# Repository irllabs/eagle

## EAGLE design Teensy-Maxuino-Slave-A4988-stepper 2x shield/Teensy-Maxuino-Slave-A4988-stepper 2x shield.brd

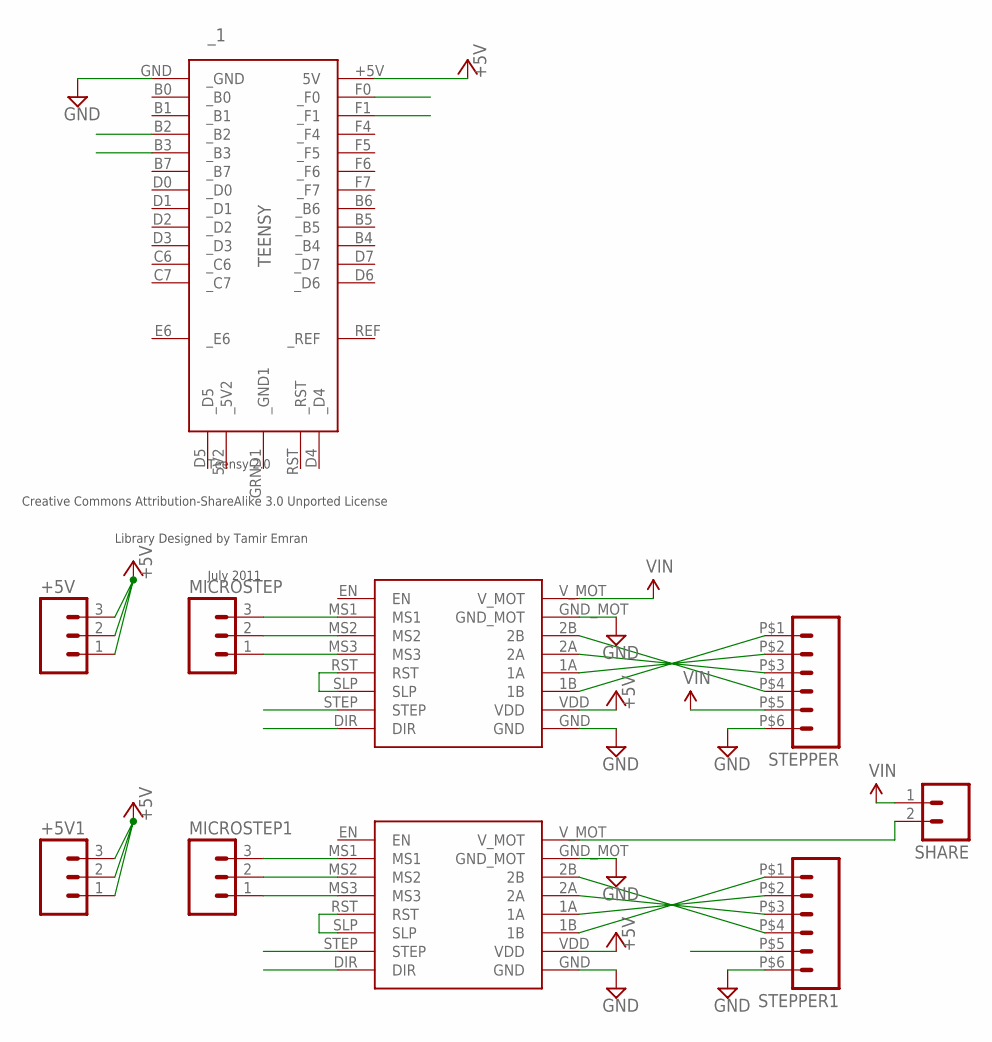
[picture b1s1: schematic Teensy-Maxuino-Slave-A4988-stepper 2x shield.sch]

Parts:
+5V, +5V1: M03PTH; 1X03
A4988_1, A4988_2: POLOLU_A4988
MICROSTEP, MICROSTEP1: M03PTH; 1X03
SHARE: M02PTH; 1X02
STEPPER, STEPPER1: M06; SPRINGTERMINAL-2.54MM-6
_1: TEENSY

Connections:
+5V: +5V.1, +5V.2, +5V.3, +5V1.1, +5V1.2, +5V1.3, A4988_1.VDD, A4988_2.VDD, _1.+5V (5V)
DIR: A4988_1.DIR, _1.F0 (_F0)
DIR1: A4988_2.DIR, _1.B3 (_B3)
GND: A4988_1.GND, A4988_1.GND_MOT, A4988_2.GND, A4988_2.GND_MOT, STEPPER.P$6 (6), STEPPER1.P$6 (6), _1.GND (_GND)
unnamed: A4988_1.2B, STEPPER.P$4 (4)
unnamed: A4988_1.2A, STEPPER.P$3 (3)
unnamed: A4988_1.1A, STEPPER.P$2 (2)
unnamed: A4988_1.1B, STEPPER.P$1 (1)
unnamed: A4988_2.RST, A4988_2.SLP
unnamed: A4988_1.RST, A4988_1.SLP
unnamed: A4988_2.MS1, MICROSTEP1.3
unnamed: A4988_1.MS1, MICROSTEP.3
unnamed: A4988_1.MS2, MICROSTEP.2
unnamed: A4988_1.MS3, MICROSTEP.1
unnamed: A4988_2.MS2, MICROSTEP1.2
unnamed: A4988_2.MS3, MICROSTEP1.1
unnamed: A4988_2.2B, STEPPER1.P$4 (4)
unnamed: A4988_2.2A, STEPPER1.P$3 (3)
unnamed: A4988_2.1A, STEPPER1.P$2 (2)
unnamed: A4988_2.1B, STEPPER1.P$1 (1)
STEP: A4988_1.STEP, _1.F1 (_F1)
STEP1: A4988_2.STEP, _1.B2 (_B2)
VIN: A4988_1.V_MOT, SHARE.1, STEPPER.P$5 (5)
VIN_2: A4988_2.V_MOT, SHARE.2, STEPPER1.P$5 (5)

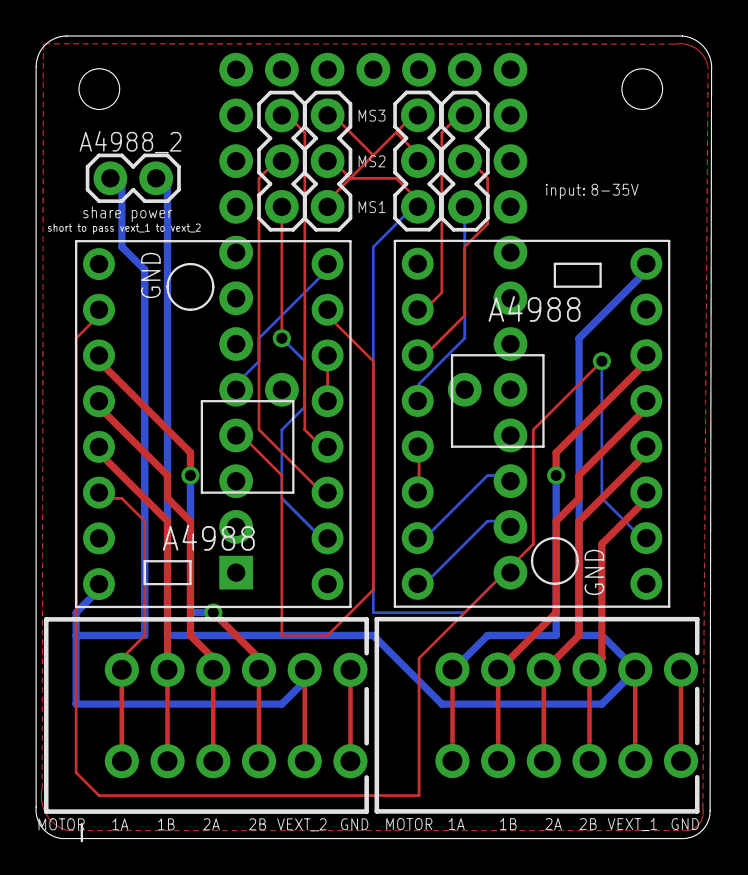
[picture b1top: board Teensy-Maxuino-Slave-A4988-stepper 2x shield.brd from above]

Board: 2 copper layers, 37.5 x 44.6 mm, 10 parts (1 on the bottom side), 24 nets.

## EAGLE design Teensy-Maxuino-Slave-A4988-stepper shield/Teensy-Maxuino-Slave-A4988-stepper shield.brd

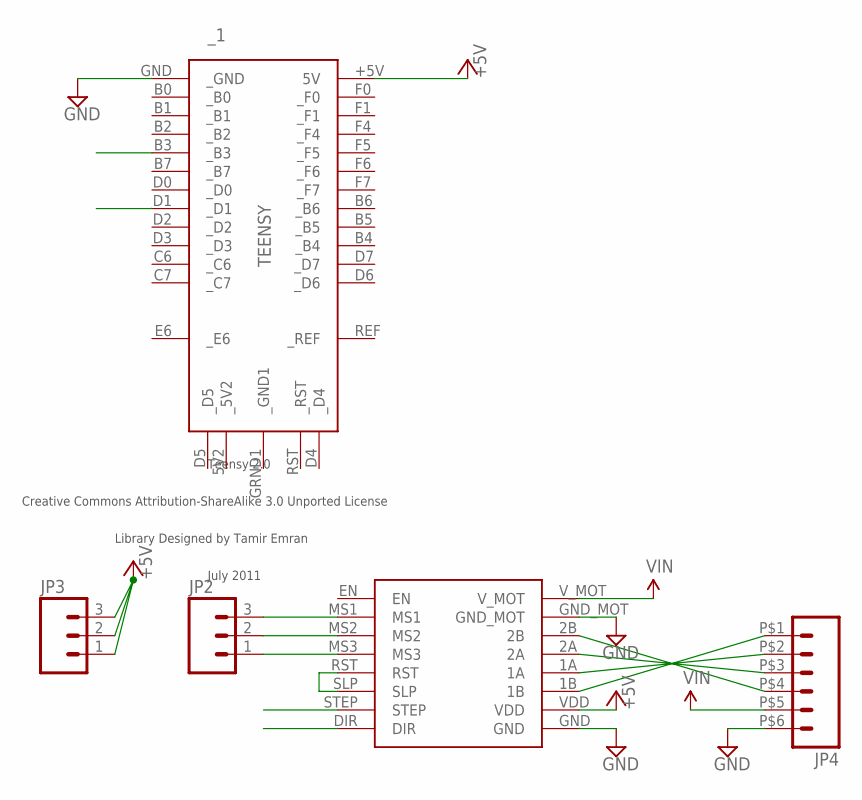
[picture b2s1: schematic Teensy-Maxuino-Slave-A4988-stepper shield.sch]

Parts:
JP2, JP3: M03PTH; 1X03
JP4: M06; SPRINGTERMINAL-2.54MM-6
U$1: POLOLU_A4988
_1: TEENSY

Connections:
+5V: JP3.1, JP3.2, JP3.3, U$1.VDD, _1.+5V (5V)
DIR: U$1.DIR, _1.D1 (_D1)
GND: JP4.P$6 (6), U$1.GND, U$1.GND_MOT, _1.GND (_GND)
unnamed: JP4.P$4 (4), U$1.2B
unnamed: JP4.P$3 (3), U$1.2A
unnamed: JP4.P$2 (2), U$1.1A
unnamed: JP4.P$1 (1), U$1.1B
unnamed: U$1.RST, U$1.SLP
unnamed: JP2.3, U$1.MS1
unnamed: JP2.2, U$1.MS2
unnamed: JP2.1, U$1.MS3
STEP: U$1.STEP, _1.B3 (_B3)
VIN: JP4.P$5 (5), U$1.V_MOT

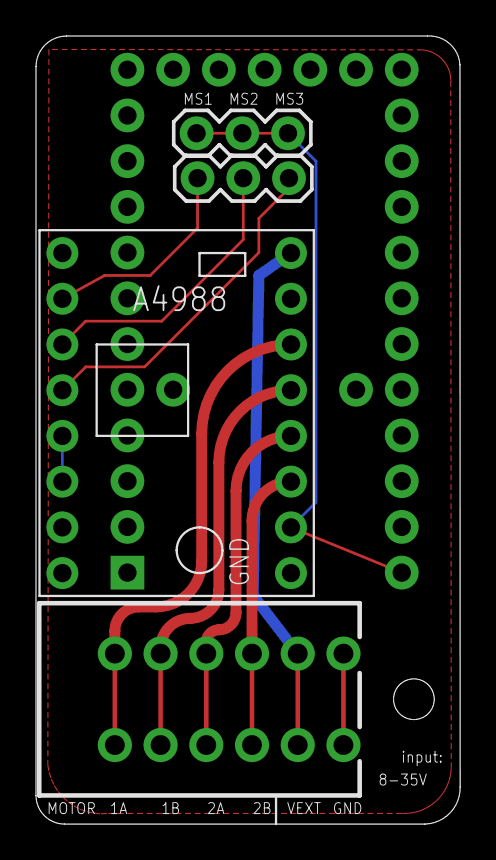
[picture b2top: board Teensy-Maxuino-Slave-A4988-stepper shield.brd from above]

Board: 2 copper layers, 23.6 x 43.8 mm, 5 parts (1 on the bottom side), 13 nets.

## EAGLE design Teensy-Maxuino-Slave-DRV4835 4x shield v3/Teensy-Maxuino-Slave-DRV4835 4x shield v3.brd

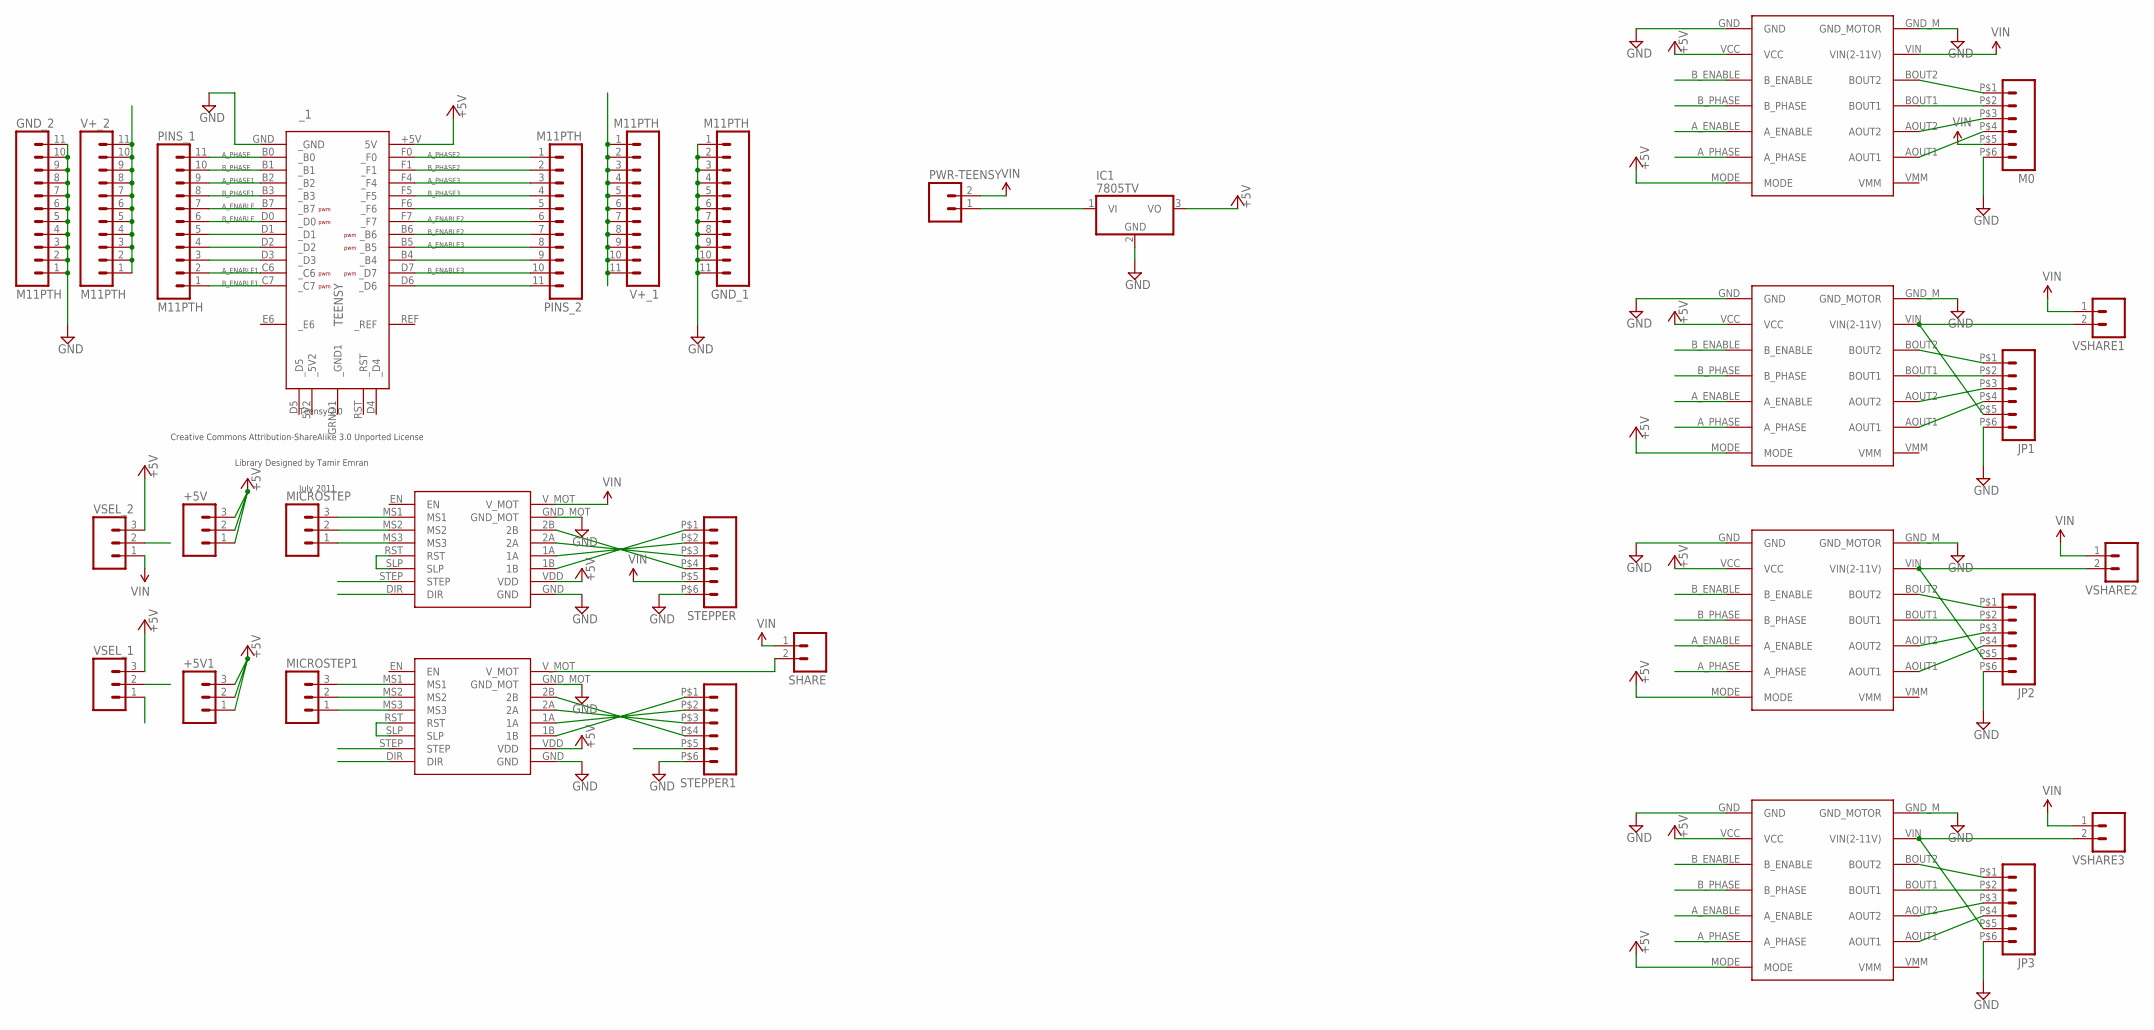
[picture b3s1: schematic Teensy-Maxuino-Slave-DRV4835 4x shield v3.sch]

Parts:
+5V, +5V1: M03PTH; 1X03
A4988_1, A4988_2: POLOLU_A4988
DRV0, DRV1, DRV2, DRV3: POLOLU_DRV8835
GND_1, GND_2: M11PTH; 1X11
IC1: 7805TV; TO220V
JP1, JP2, JP3: M06; SPRINGTERMINAL-2.54MM-6
M0: M06; SPRINGTERMINAL-2.54MM-6
MICROSTEP, MICROSTEP1: M03PTH; 1X03
PINS_1, PINS_2: M11PTH; 1X11
PWR-TEENSY: M02PTH; 1X02
SHARE: M02PTH; 1X02
STEPPER, STEPPER1: M06; SPRINGTERMINAL-2.54MM-6
V+_1, V+_2: M11PTH; 1X11
VSEL_1, VSEL_2: M03PTH; 1X03
VSHARE1, VSHARE2, VSHARE3: M02PTH; 1X02
_1: TEENSY

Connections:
+5V: +5V.1, +5V.2, +5V.3, +5V1.1, +5V1.2, +5V1.3, A4988_1.VDD, A4988_2.VDD, DRV0.MODE, DRV0.VCC, DRV1.MODE, DRV1.VCC, DRV2.MODE, DRV2.VCC, DRV3.MODE, DRV3.VCC, IC1.3 (VO), VSEL_1.3, VSEL_2.3, _1.+5V (5V)
ATTRU: JP1.P$6 (6), JP2.P$6 (6), JP3.P$6 (6), M0.P$6 (6)
A_ENABLE: DRV0.A_ENABLE, PINS_1.7, _1.B7 (_B7)
A_ENABLE1: DRV1.A_ENABLE, PINS_1.2, _1.C6 (_C6)
A_ENABLE2: DRV2.A_ENABLE, PINS_2.6, _1.F7 (_F7)
A_ENABLE3: DRV3.A_ENABLE, PINS_2.8, _1.B5 (_B5)
A_PHASE: DRV0.A_PHASE, PINS_1.11, _1.B0 (_B0)
A_PHASE1: DRV1.A_PHASE, PINS_1.9, _1.B2 (_B2)
A_PHASE2: DRV2.A_PHASE, PINS_2.1, _1.F0 (_F0)
A_PHASE3: DRV3.A_PHASE, PINS_2.3, _1.F4 (_F4)
B_ENABLE: DRV0.B_ENABLE, PINS_1.6, _1.D0 (_D0)
B_ENABLE1: DRV1.B_ENABLE, PINS_1.1, _1.C7 (_C7)
B_ENABLE2: DRV2.B_ENABLE, PINS_2.7, _1.B6 (_B6)
B_ENABLE3: DRV3.B_ENABLE, PINS_2.10, _1.D7 (_D7)
B_PHASE: DRV0.B_PHASE, PINS_1.10, _1.B1 (_B1)
B_PHASE1: DRV1.B_PHASE, PINS_1.4, PINS_1.8, _1.B3 (_B3), _1.D2 (_D2)
B_PHASE2: DRV2.B_PHASE, PINS_2.2, _1.F1 (_F1)
B_PHASE3: DRV3.B_PHASE, PINS_2.4, _1.F5 (_F5)
DIR: A4988_1.DIR, PINS_2.11, _1.D6 (_D6)
DIR1: A4988_2.DIR, PINS_1.5, _1.D1 (_D1)
GND: A4988_1.GND, A4988_1.GND_MOT, A4988_2.GND, A4988_2.GND_MOT, DRV0.GND, DRV0.GND_M (GND_MOTOR), DRV1.GND, DRV1.GND_M (GND_MOTOR), DRV2.GND, DRV2.GND_M (GND_MOTOR), DRV3.GND, DRV3.GND_M (GND_MOTOR), GND_1.1, GND_1.2, GND_1.3, GND_1.4, GND_1.5, GND_1.6, GND_1.7, GND_1.8, GND_1.9, GND_1.10, GND_1.11, GND_2.1, GND_2.2, GND_2.3, GND_2.4, GND_2.5, GND_2.6, GND_2.7, GND_2.8, GND_2.9, GND_2.10, GND_2.11, IC1.2 (GND), STEPPER.P$6 (6), STEPPER1.P$6 (6), _1.GND (_GND)
unnamed: A4988_1.2B, STEPPER.P$4 (4)
unnamed: A4988_1.2A, STEPPER.P$3 (3)
unnamed: A4988_1.1A, STEPPER.P$2 (2)
unnamed: A4988_1.1B, STEPPER.P$1 (1)
unnamed: A4988_2.RST, A4988_2.SLP
unnamed: A4988_1.RST, A4988_1.SLP
unnamed: A4988_2.MS1, MICROSTEP1.3
unnamed: A4988_1.MS1, MICROSTEP.3
unnamed: A4988_1.MS2, MICROSTEP.2
unnamed: A4988_1.MS3, MICROSTEP.1
unnamed: A4988_2.MS2, MICROSTEP1.2
unnamed: A4988_2.MS3, MICROSTEP1.1
unnamed: A4988_2.2B, STEPPER1.P$4 (4)
unnamed: A4988_2.2A, STEPPER1.P$3 (3)
unnamed: A4988_2.1A, STEPPER1.P$2 (2)
unnamed: A4988_2.1B, STEPPER1.P$1 (1)
unnamed: PINS_1.3, _1.D3 (_D3)
unnamed: PINS_2.5, _1.F6 (_F6)
unnamed: DRV0.AOUT1, M0.P$4 (4)
unnamed: DRV0.AOUT2, M0.P$3 (3)
unnamed: DRV0.BOUT1, M0.P$2 (2)
unnamed: DRV0.BOUT2, M0.P$1 (1)
unnamed: DRV1.AOUT1, JP1.P$4 (4)
unnamed: DRV1.AOUT2, JP1.P$3 (3)
unnamed: DRV1.BOUT1, JP1.P$2 (2)
unnamed: DRV1.BOUT2, JP1.P$1 (1)
unnamed: DRV2.AOUT1, JP2.P$4 (4)
unnamed: DRV2.AOUT2, JP2.P$3 (3)
unnamed: DRV2.BOUT1, JP2.P$2 (2)
unnamed: DRV2.BOUT2, JP2.P$1 (1)
unnamed: DRV3.AOUT1, JP3.P$4 (4)
unnamed: DRV3.AOUT2, JP3.P$3 (3)
unnamed: DRV3.BOUT1, JP3.P$2 (2)
unnamed: DRV3.BOUT2, JP3.P$1 (1)
unnamed: IC1.1 (VI), PWR-TEENSY.1
STEP: A4988_1.STEP, PINS_2.9, _1.B4 (_B4)
STEP1: A4988_2.STEP
V+_1: V+_1.1, V+_1.2, V+_1.3, V+_1.4, V+_1.5, V+_1.6, V+_1.7, V+_1.8, V+_1.9, V+_1.10, V+_1.11, VSEL_1.2
V+_2: V+_2.1, V+_2.2, V+_2.3, V+_2.4, V+_2.5, V+_2.6, V+_2.7, V+_2.8, V+_2.9, V+_2.10, V+_2.11, VSEL_2.2
VIN: A4988_1.V_MOT, DRV0.VIN (VIN(2-11V)), M0.P$5 (5), PWR-TEENSY.2, SHARE.1, STEPPER.P$5 (5), VSEL_2.1, VSHARE1.1, VSHARE2.1, VSHARE3.1
VIN1: DRV1.VIN (VIN(2-11V)), JP1.P$5 (5), VSHARE1.2
VIN2: DRV2.VIN (VIN(2-11V)), JP2.P$5 (5), VSHARE2.2
VIN3: DRV3.VIN (VIN(2-11V)), JP3.P$5 (5), VSHARE3.2
VIN_2: A4988_2.V_MOT, SHARE.2, STEPPER1.P$5 (5), VSEL_1.1

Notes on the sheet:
B_PHASE1
A_PHASE
B_PHASE
A_PHASE1
A_ENABLE
B_ENABLE
A_ENABLE1
B_ENABLE1
B_PHASE3
A_PHASE2
B_PHASE2
A_PHASE3
A_ENABLE2
B_ENABLE2
A_ENABLE3
B_ENABLE3

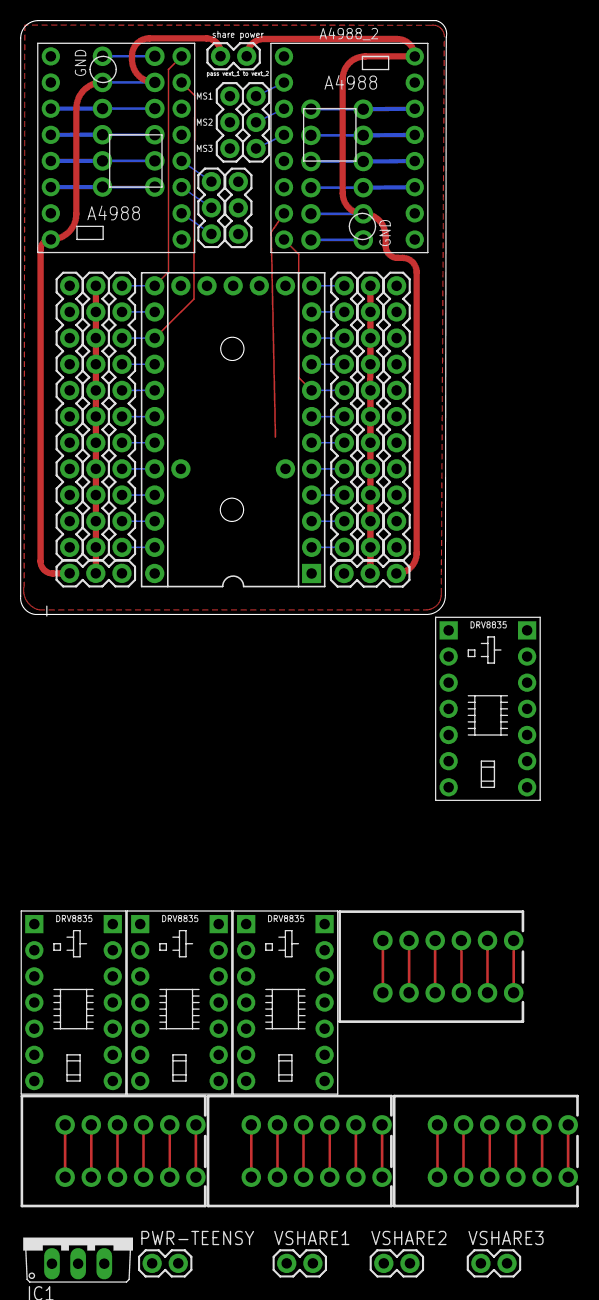
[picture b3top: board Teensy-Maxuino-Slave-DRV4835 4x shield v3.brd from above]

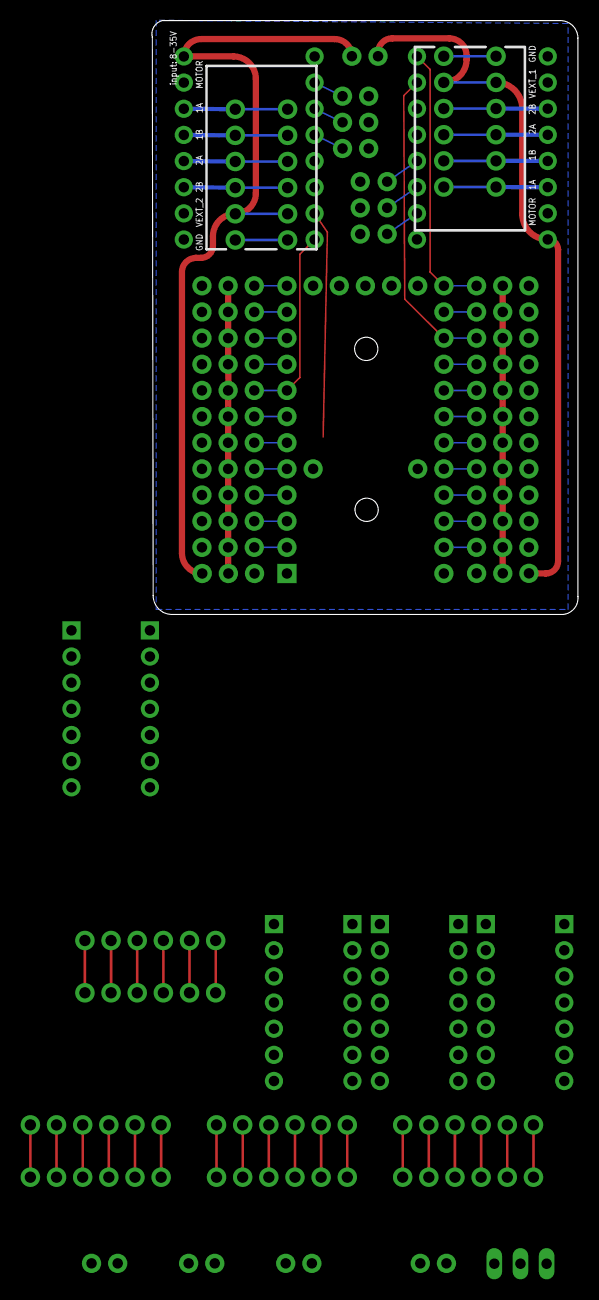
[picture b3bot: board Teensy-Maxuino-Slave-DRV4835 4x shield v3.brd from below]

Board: 2 copper layers, 41.4 x 57.7 mm, 31 parts (2 on the bottom side), 64 nets.

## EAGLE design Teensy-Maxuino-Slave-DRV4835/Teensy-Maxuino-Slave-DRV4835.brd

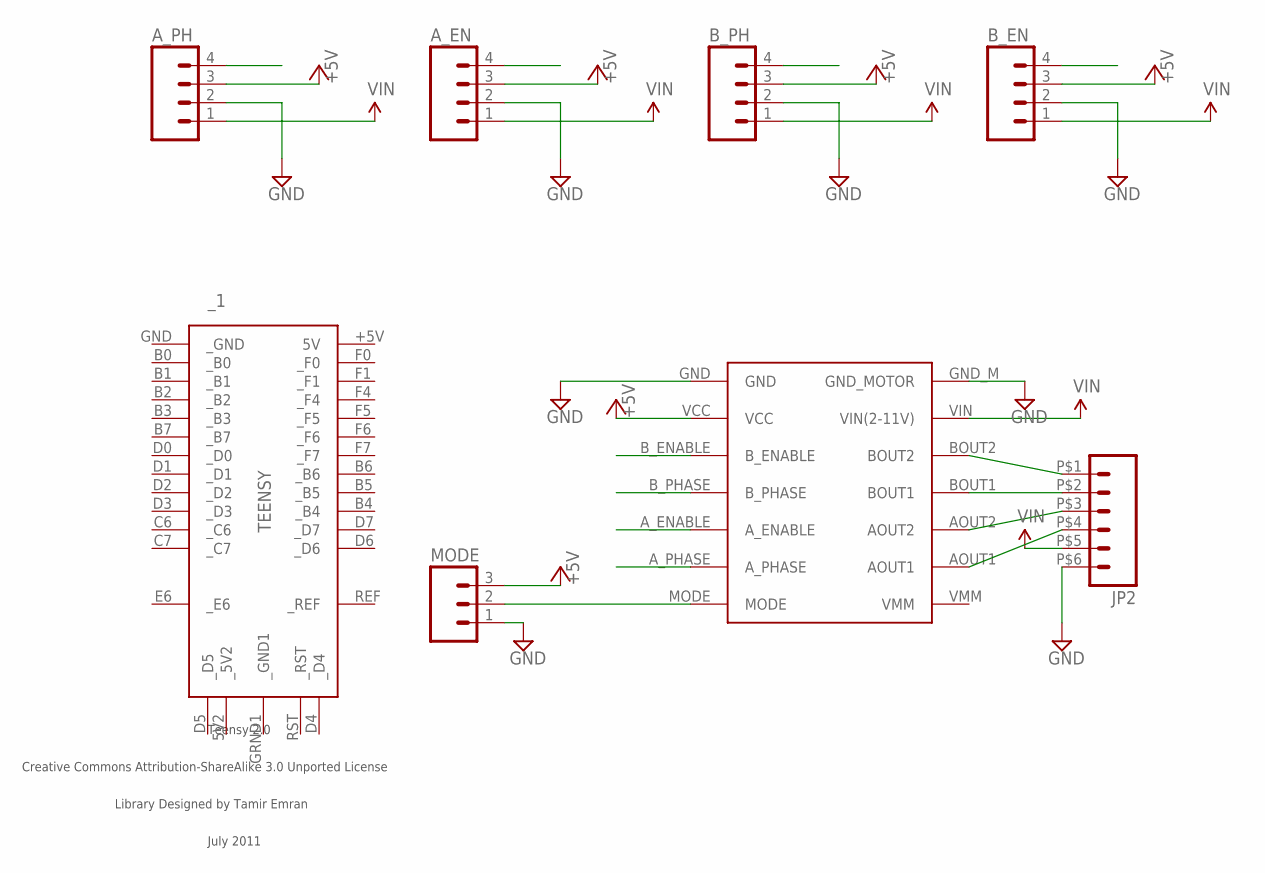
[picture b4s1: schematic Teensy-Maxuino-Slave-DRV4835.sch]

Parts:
A_EN: M04PTH; 1X04
A_PH: M04PTH; 1X04
B_EN: M04PTH; 1X04
B_PH: M04PTH; 1X04
DRV8835: POLOLU_DRV8835
JP2: M06; SPRINGTERMINAL-2.54MM-6
MODE: M03PTH; 1X03
_1: TEENSY

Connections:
+5V: A_EN.3, A_PH.3, B_EN.3, B_PH.3, DRV8835.VCC, MODE.3
A-ENABLE: A_EN.4, DRV8835.A_ENABLE
A-PHASE: A_PH.4, DRV8835.A_PHASE
ATTRU: A_EN.2, A_PH.2, B_EN.2, B_PH.2, DRV8835.GND, DRV8835.GND_M (GND_MOTOR), JP2.P$6 (6), MODE.1
B-ENABLE: B_EN.4, DRV8835.B_ENABLE
B-PHASE: B_PH.4, DRV8835.B_PHASE
unnamed: DRV8835.AOUT1, JP2.P$4 (4)
unnamed: DRV8835.AOUT2, JP2.P$3 (3)
unnamed: DRV8835.BOUT1, JP2.P$2 (2)
unnamed: DRV8835.BOUT2, JP2.P$1 (1)
unnamed: DRV8835.MODE, MODE.2
VIN: A_EN.1, A_PH.1, B_EN.1, B_PH.1, DRV8835.VIN (VIN(2-11V)), JP2.P$5 (5)

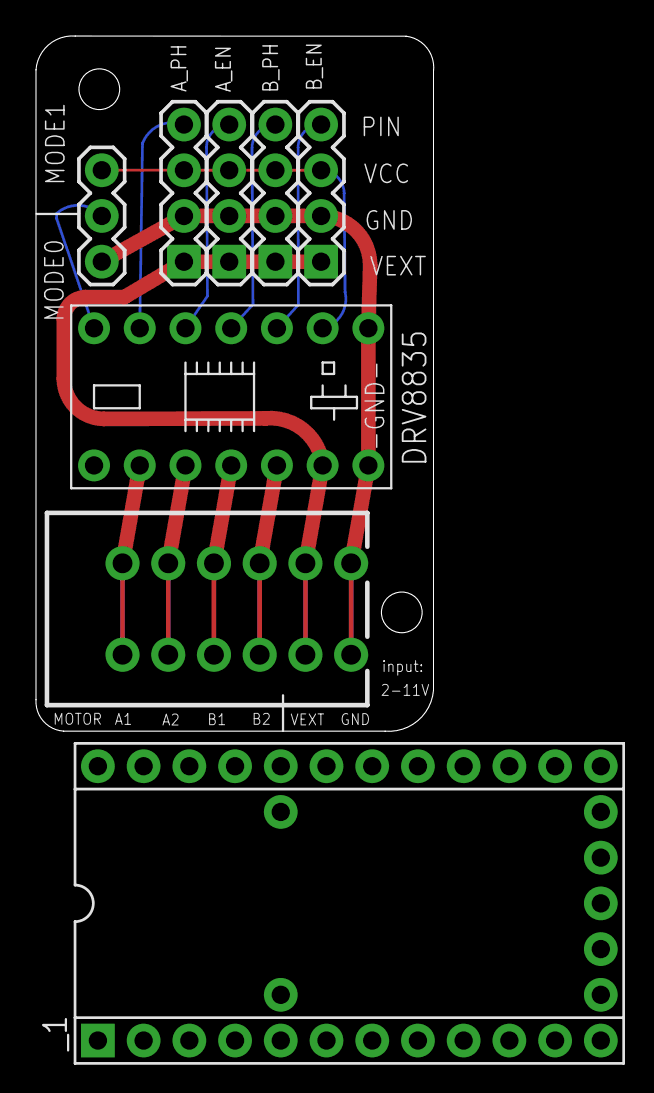
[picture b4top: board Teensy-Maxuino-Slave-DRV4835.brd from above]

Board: 2 copper layers, 22.1 x 38.6 mm, 8 parts (0 on the bottom side), 12 nets.

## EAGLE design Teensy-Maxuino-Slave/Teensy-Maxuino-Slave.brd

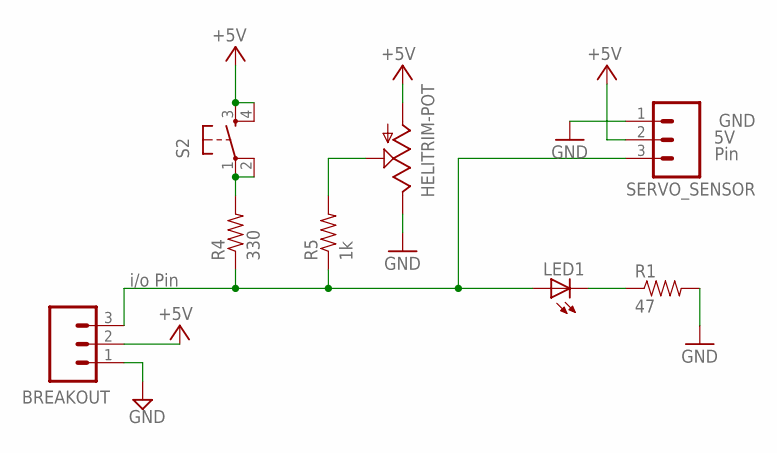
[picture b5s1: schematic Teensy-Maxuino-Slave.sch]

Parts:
BREAKOUT: M03PTH; 1X03
LED1: LED3MM
R1: 47; 1/6W-RES
R4: 330; 1/6W-RES
R5: 1k; 1/6W-RES
S2: TAC_SWITCHPTH; TACTILE-PTH
SERVO_SENSOR: M03PTH; 1X03
U$1: HELITRIM-POT

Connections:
+5V: BREAKOUT.2, S2.3, S2.4, SERVO_SENSOR.2, U$1.P$1 (A)
GND: BREAKOUT.1, R1.2, SERVO_SENSOR.1, U$1.P$2 (E)
unnamed: R4.2, S2.1, S2.2
unnamed: R5.2, U$1.P$3 (S)
unnamed: LED1.K (C), R1.1
PIN: BREAKOUT.3, LED1.A, R4.1, R5.1, SERVO_SENSOR.3

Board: 2 copper layers, 8 parts (0 on the bottom side), 6 nets, no tracks yet.

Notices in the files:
parts and their libraries:
SparkFun-Connectors: Licensing: CC v3.0 Share-Alike You are welcome to use this library for commercial purposes.
aliEagleLib: Licensed Under Creative Commons
aliEagleLib: Creative Commons Attribution-ShareAlike 3.0 Unported License
